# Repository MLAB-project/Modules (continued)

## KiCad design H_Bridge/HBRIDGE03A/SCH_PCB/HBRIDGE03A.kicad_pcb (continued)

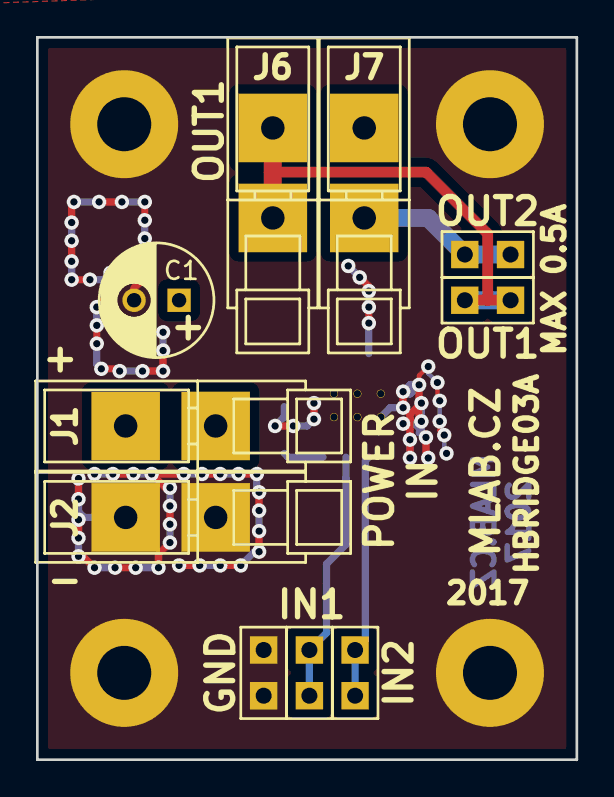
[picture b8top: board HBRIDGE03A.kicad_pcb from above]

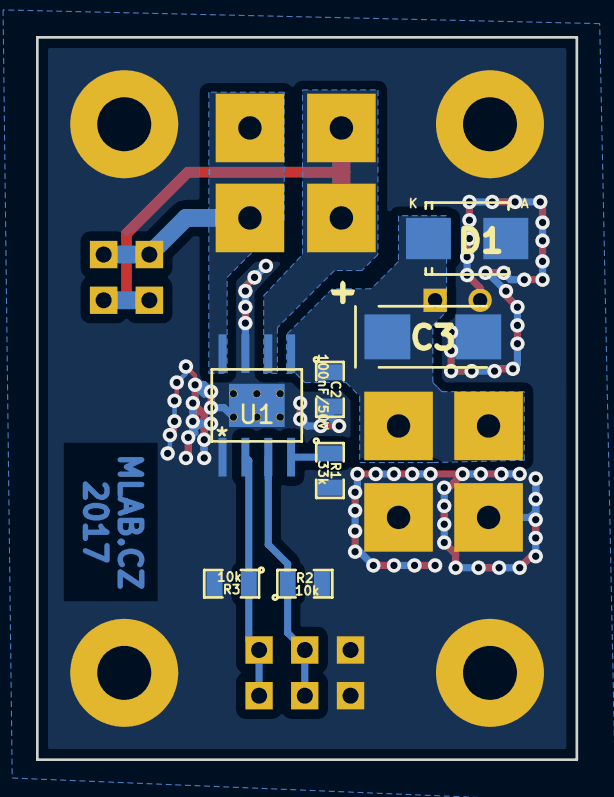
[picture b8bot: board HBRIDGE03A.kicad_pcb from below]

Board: 2 copper layers, 30.0 x 40.1 mm, 21 parts (7 on the bottom side), 7 nets.
